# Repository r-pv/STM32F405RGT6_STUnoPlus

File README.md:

# STM32F405RGT6 STUno+

An ST development board based on the STM32F405RGT6/STM32F405RG (Clock: 168MHz, Flash: 1024Kb, Ram:194Kb) MCU (LQFP-64) compatible with STM32Duino (Arduino).

## Pinout:

## Files and Folders description

- **RBOARD_F405RGT6** it's the variant board for the STM32 Arduino Core.
- **rSTM32F405RGT6_B** it's the KiCAD 5.1.2 project.
- **rSTM32F405RGT6.schematic.pdf** the schematic.

## Install

- This requires the [STM32 core for arduino](https://github.com/stm32duino/Arduino_Core_STM32/), the ST original.
- I used this [guide to add the board](https://github.com/stm32duino/wiki/wiki/Add-a-new-variant-(board)), you can check it or continue with my suggestions to install the new board.
- Copy the **"RBOARD_F405RGT6"** folder to the Arduino **"variants"** folder, in win7 is located at: **c:\Users\\<USERNAME\>\AppData\Local\Arduino15\packages\STM32\hardware\stm32\1.8.0\variants**
- Edit the **"boards.txt"** file, in win7 is located at a lever up than the "variants" folder, search for the **Generic F4** board line and add the lines to leave it as I show you next:

```
# Adafruit Feather STM32F405 board
GenF4.menu.pnum.FEATHER_F405=Adafruit Feather STM32F405
GenF4.menu.pnum.FEATHER_F405.upload.maximum_size=1048576
GenF4.menu.pnum.FEATHER_F405.upload.maximum_data_size=131072
GenF4.menu.pnum.FEATHER_F405.build.board=FEATHER_F405
GenF4.menu.pnum.FEATHER_F405.build.product_line=STM32F405xx
GenF4.menu.pnum.FEATHER_F405.build.variant=FEATHER_F405

# STM32F405RGT6 STUnoPlus board
GenF4.menu.pnum.RBOARD_F405RGT6=STM32F405RGT6 STUnoPlus
GenF4.menu.pnum.RBOARD_F405RGT6.upload.maximum_size=1048576
GenF4.menu.pnum.RBOARD_F405RGT6.upload.maximum_data_size=131072
GenF4.menu.pnum.RBOARD_F405RGT6.build.board=RBOARD_F405RGT6
GenF4.menu.pnum.RBOARD_F405RGT6.build.product_line=STM32F405xx
GenF4.menu.pnum.RBOARD_F405RGT6.build.variant=RBOARD_F405RGT6
```
(add after the _"# Adafruit Feather STM32F405 board"_ section).

That's all.

So on the arduino IDE, on the **boards** menu pick the option _"Generic STM32F4 series"_ and the **board part number:** suboption pick the _"STM32F405RGT6 STUnoPlus"_ option.

**Note:** while adafruit board and mine use the same MCU there are not compatible variants: adafruit uses a 12mhz external crystal, mine uses an 8mhz.

## The real board

**Front**

_*I submerge the boards on a painters solvent bath to clean the flux residue which I haven't any problem until the DC jack came, as you see, didn't took the solvent bath kindly :P_

**Back**

_*The footprint for the second crystal (Y2) was wrong on this board but it's already corrected on the KiCAD files._

## Running some tests

The **STUno+** running the Adafruit ILI9341 library over hardware SPI.

_Video in progress..._

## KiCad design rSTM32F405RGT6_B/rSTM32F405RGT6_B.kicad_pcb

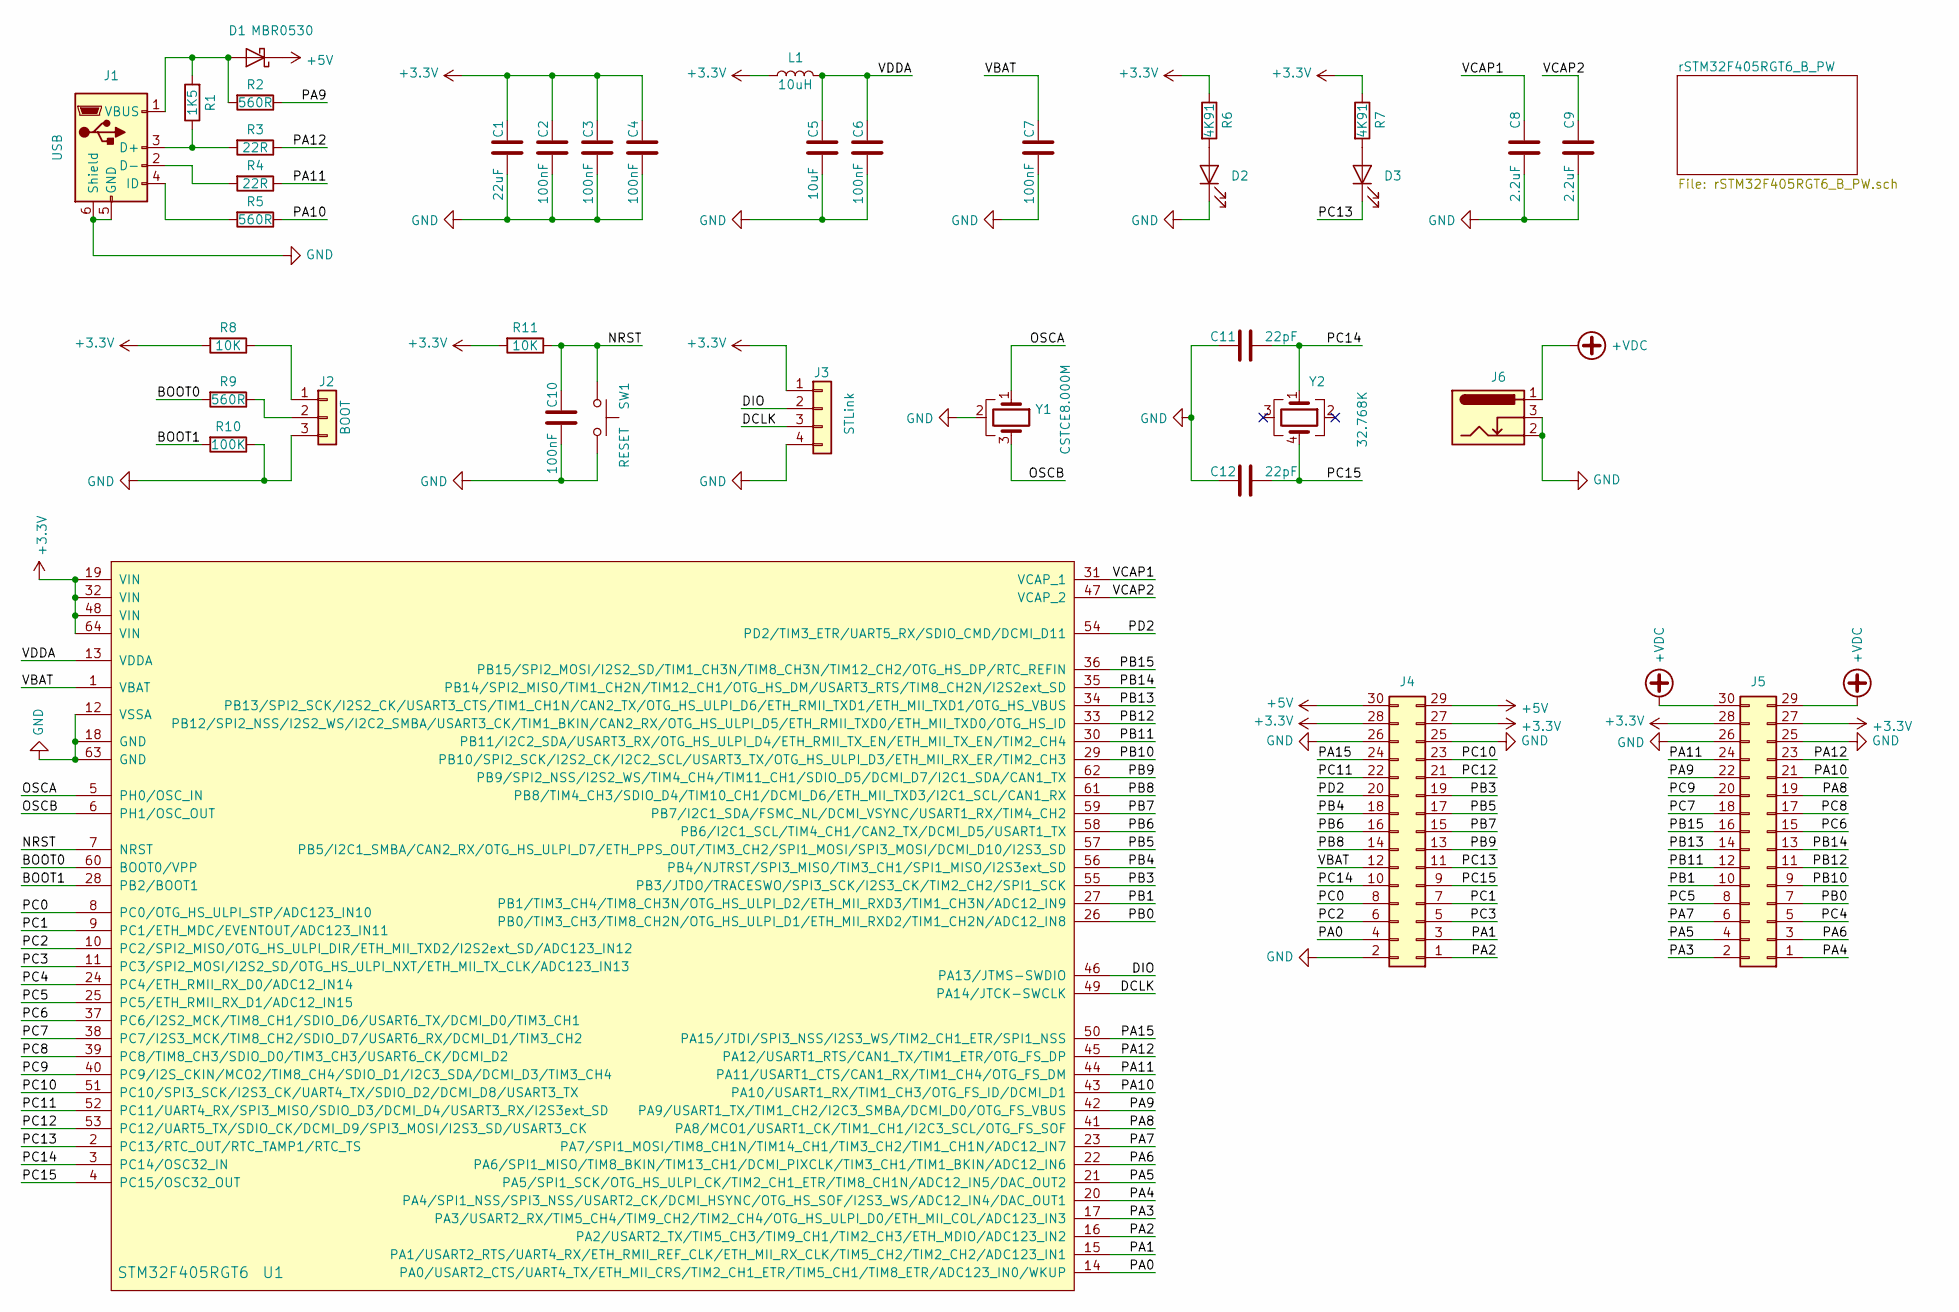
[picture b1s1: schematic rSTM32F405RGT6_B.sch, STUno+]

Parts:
C1: 22uF; C_0805
C2, C3, C4, C6, C7, C10: 100nF; C_0805
C5: 10uF; C_0805
C8, C9: 2.2uF; C_0603
C11, C12: 22pF; C_0805
D1: MBR0530; D_SOD-123
D2, D3: LED; LED_0805
J1: USB; USB_Micro-B_Molex_47346-0001
J2: BOOT; Pin_Header_Straight_1x03_Pitch2.54mm
J3: STLink; Pin_Header_Straight_1x04_Pitch2.54mm
J4, J5: Pin_Header_Straight_2x15_Pitch2.54mm
J6: JACK_ALIM
L1: 10uH; L_0805
R1: 1K5; R_0603
R2, R5, R9: 560R; R_0603
R3, R4: 22R; R_0603
R6, R7: 4K91; R_0603
R8, R11: 10K; R_0603
R10: 100K; R_0603
SW1: RESET; Switch_SMD_5.2x6.4_reset
U1: STM32F405RGT6; LQFP-64_10x10mm_Pitch0.5mm
Y1: CSTCE8.000M; Crystal_CSTCE_3pin_3.2x1.3
Y2: 32.768K; Crystal_4pin_SMD_2.5x4.6

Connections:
+3V3: C1.1, C2.1, C3.1, C4.1, J3.1, J4.27, J4.28, J5.27, J5.28, L1.1, R6.1, R7.1, R8.2, R11.2, U1.19 (VIN), U1.32 (VIN), U1.48 (VIN), U1.64 (VIN); also elsewhere on the board
+5V: D1.1 (K), J4.29, J4.30; also elsewhere on the board
+VDC: J5.29, J5.30, J6.1; also elsewhere on the board
/BOOT0: R9.2, U1.60 (BOOT0/VPP)
/BOOT1: R10.2, U1.28 (PB2/BOOT1)
/DCLK: J3.3, U1.49 (PA14/JTCK-SWCLK)
/DIO: J3.2, U1.46 (PA13/JTMS-SWDIO)
/NRST: C10.1, R11.1, SW1.1, U1.7 (NRST)
/OSCA: U1.5 (PH0/OSC_IN), Y1.1
/OSCB: U1.6 (PH1/OSC_OUT), Y1.3
/PA0: J4.4, U1.14 (PA0/USART2_CTS/UART4_TX/ETH_MII_CRS/TIM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)
/PA1: J4.3, U1.15 (PA1/USART2_RTS/UART4_RX/ETH_RMII_REF_CL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)
/PA2: J4.1, U1.16 (PA2/USART2_TX/TIM5_CH3/TIM9_CH1/TIM2_CH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)
/PA3: J5.2, U1.17 (PA3/USART2_RX/TIM5_CH4/TIM9_CH2/TIM2_CH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)
/PA4: J5.1, U1.20 (PA4/SPI1_NSS/SPI3_NSS/USART2_CK/DCMI_HS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)
/PA5: J5.4, U1.21 (PA5/SPI1_SCK/OTG_HS_ULPI_CK/TIM2_CH1_ET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)
/PA6: J5.3, U1.22 (PA6/SPI1_MISO/TIM8_BKIN/TIM13_CH1/DCMI_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)
/PA7: J5.6, U1.23 (PA7/SPI1_MOSI/TIM8_CH1N/TIM14_CH1/TIM3_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)
/PA8: J5.19, U1.41 (PA8/MCO1/USART1_CK/TIM1_CH1/I2C3_SCL/OT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)
/PA9: J5.22, R2.1, U1.42 (PA9/USART1_TX/TIM1_CH2/I2C3_SMBA/DCMI_D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)
/PA10: J5.21, R5.1, U1.43 (PA10/USART1_RX/TIM1_CH3/OTG_FS_ID/DCMI_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)
/PA11: J5.24, R4.1, U1.44 (PA11/USART1_CTS/CAN1_RX/TIM1_CH4/OTG_FS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)
/PA12: J5.23, R3.1, U1.45 (PA12/USART1_RTS/CAN1_TX/TIM1_ETR/OTG_FS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)
/PA15: J4.24, U1.50 (PA15/JTDI/SPI3_NSS/I2S3_WS/TIM2_CH1_ETR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)
/PB0: J5.7, U1.26 (PB0/TIM3_CH3/TIM8_CH2N/OTG_HS_ULPI_D1/E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)
/PB1: J5.10, U1.27 (PB1/TIM3_CH4/TIM8_CH3N/OTG_HS_ULPI_D2/E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)
/PB3: J4.19, U1.55 (PB3/JTDO/TRACESWO/SPI3_SCK/I2S3_CK/TIM2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)
/PB4: J4.18, U1.56 (PB4/NJTRST/SPI3_MISO/TIM3_CH1/SPI1_MISO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)
/PB5: J4.17, U1.57 (PB5/I2C1_SMBA/CAN2_RX/OTG_HS_ULPI_D7/ET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)
/PB6: J4.16, U1.58 (PB6/I2C1_SCL/TIM4_CH1/CAN2_TX/DCMI_D5/U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)
/PB7: J4.15, U1.59 (PB7/I2C1_SDA/FSMC_NL/DCMI_VSYNC/USART1_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)
/PB8: J4.14, U1.61 (PB8/TIM4_CH3/SDIO_D4/TIM10_CH1/DCMI_D6/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)
/PB9: J4.13, U1.62 (PB9/SPI2_NSS/I2S2_WS/TIM4_CH4/TIM11_CH1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)
/PB10: J5.9, U1.29 (PB10/SPI2_SCK/I2S2_CK/I2C2_SCL/USART3_T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)
/PB11: J5.12, U1.30 (PB11/I2C2_SDA/USART3_RX/OTG_HS_ULPI_D4/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)
/PB12: J5.11, U1.33 (PB12/SPI2_NSS/I2S2_WS/I2C2_SMBA/USART3_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)
/PB13: J5.14, U1.34 (PB13/SPI2_SCK/I2S2_CK/USART3_CTS/TIM1_C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)
/PB14: J5.13, U1.35 (PB14/SPI2_MISO/TIM1_CH2N/TIM12_CH1/OTG_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)
/PB15: J5.16, U1.36 (PB15/SPI2_MOSI/I2S2_SD/TIM1_CH3N/TIM8_C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)
/PC0: J4.8, U1.8 (PC0/OTG_HS_ULPI_STP/ADC123_IN10)
/PC1: J4.7, U1.9 (PC1/ETH_MDC/EVENTOUT/ADC123_IN11)
/PC2: J4.6, U1.10 (PC2/SPI2_MISO/OTG_HS_ULPI_DIR/ETH_MII_T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)
/PC3: J4.5, U1.11 (PC3/SPI2_MOSI/I2S2_SD/OTG_HS_ULPI_NXT/E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)
/PC4: J5.5, U1.24 (PC4/ETH_RMII_RX_D0/ADC12_IN14)
/PC5: J5.8, U1.25 (PC5/ETH_RMII_RX_D1/ADC12_IN15)
/PC6: J5.15, U1.37 (PC6/I2S2_MCK/TIM8_CH1/SDIO_D6/USART6_TX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)
/PC7: J5.18, U1.38 (PC7/I2S3_MCK/TIM8_CH2/SDIO_D7/USART6_RX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)
/PC8: J5.17, U1.39 (PC8/TIM8_CH3/SDIO_D0/TIM3_CH3/USART6_CK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)
/PC9: J5.20, U1.40 (PC9/I2S_CKIN/MCO2/TIM8_CH4/SDIO_D1/I2C3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)
/PC10: J4.23, U1.51 (PC10/SPI3_SCK/I2S3_CK/UART4_TX/SDIO_D2/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)
/PC11: J4.22, U1.52 (PC11/UART4_RX/SPI3_MISO/SDIO_D3/DCMI_D4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)
/PC12: J4.21, U1.53 (PC12/UART5_TX/SDIO_CK/DCMI_D9/SPI3_MOSI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)
/PC13: D3.1 (K), J4.11, U1.2 (PC13/RTC_OUT/RTC_TAMP1/RTC_TS)
/PC14: C11.1, J4.10, U1.3 (PC14/OSC32_IN), Y2.1
/PC15: C12.1, J4.9, U1.4 (PC15/OSC32_OUT), Y2.4
/PD2: J4.20, U1.54 (PD2/TIM3_ETR/UART5_RX/SDIO_CMD/DCMI_D11)
/VBAT: C7.1, J4.12, U1.1 (VBAT)
/VCAP1: C8.1, U1.31 (VCAP_1)
/VCAP2: C9.1, U1.47 (VCAP_2)
/VDDA: C5.1, C6.1, L1.2, U1.13 (VDDA)
GND: C1.2, C2.2, C3.2, C4.2, C5.2, C6.2, C7.2, C8.2, C9.2, C10.2, C11.2, C12.2, D2.1 (K), J1.5 (GND), J1.6 (Shield), J2.3, J3.4, J4.2, J4.25, J4.26, J5.25, J5.26, J6.2, J6.3, R10.1, SW1.2, U1.12 (VSSA), U1.18 (GND), U1.63 (GND), Y1.2; also elsewhere on the board
unnamed: D1.2 (A), J1.1 (VBUS), R1.2, R2.2
unnamed: D2.2 (A), R6.2
unnamed: D3.2 (A), R7.2
unnamed: J1.2 (D-), R4.2
unnamed: J1.3 (D+), R1.1, R3.2
unnamed: J1.4 (ID), R5.2
unnamed: J2.1, R8.1
unnamed: J2.2, R9.1

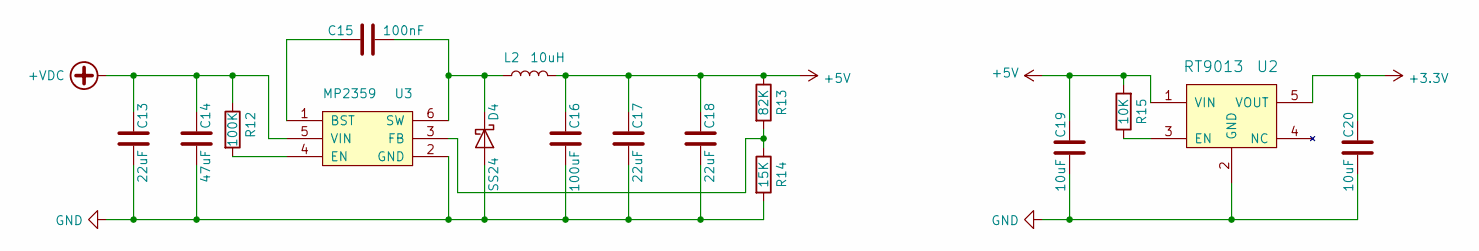
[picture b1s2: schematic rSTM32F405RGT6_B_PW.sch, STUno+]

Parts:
C13, C17, C18: 22uF; C_0805
C14: 47uF; C_1206
C15: 100nF; C_0805
C16: 100uF; C_1206
C19, C20: 10uF; C_0805
D4: SS24; D_SMA
L2: 10uH; Inductor-CD54
R12: 100K; R_0603
R13: 82K; R_0603
R14: 15K; R_0603
R15: 10K; R_0603
U2: RT9013; SOT-23-5
U3: MP2359; SOT-23-6

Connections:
+3V3: C20.1, U2.5 (VOUT); also elsewhere on the board
+5V: C16.1, C17.1, C18.1, C19.1, L2.2, R13.1, R15.2, U2.1 (VIN); also elsewhere on the board
+VDC: C13.1, C14.1, R12.1, U3.5 (VIN); also elsewhere on the board
GND: C13.2, C14.2, C16.2, C17.2, C18.2, C19.2, C20.2, D4.2 (A), R14.2, U2.2 (GND), U3.2 (GND); also elsewhere on the board
unnamed: C15.1, D4.1 (K), L2.1, U3.6 (SW)
unnamed: C15.2, U3.1 (BST)
unnamed: R12.2, U3.4 (EN)
unnamed: R13.2, R14.1, U3.3 (FB)
unnamed: R15.1, U2.3 (EN)

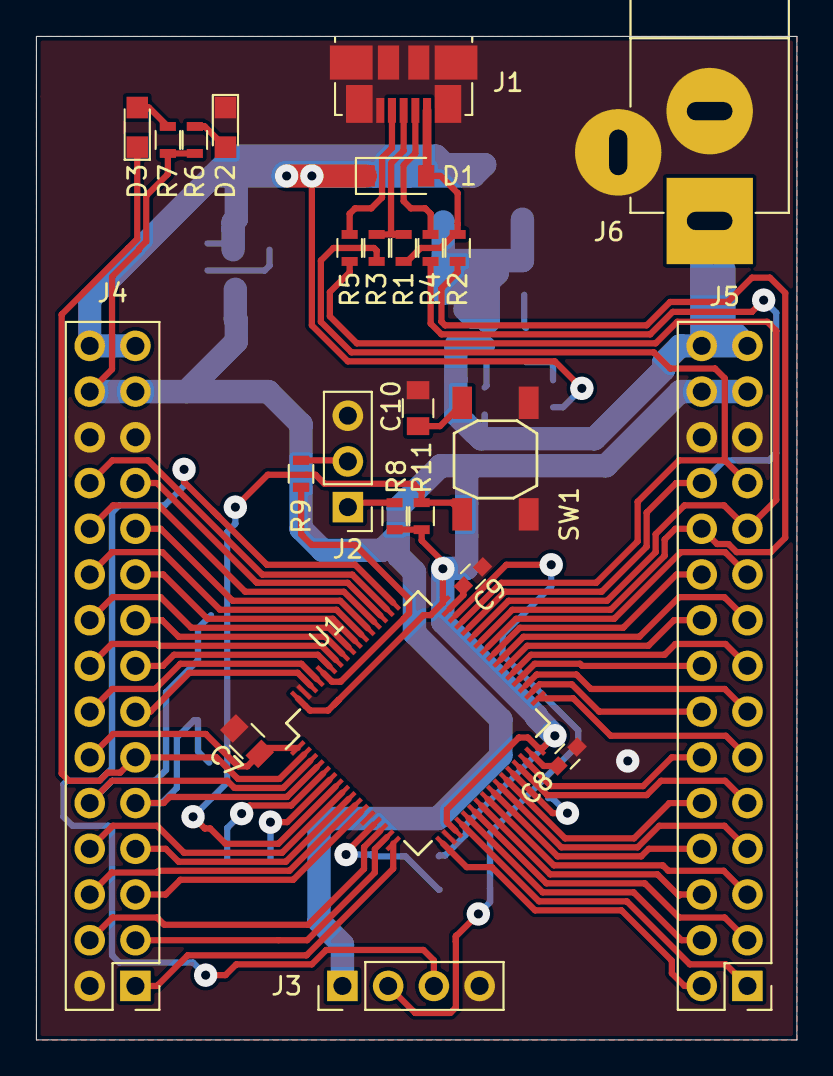
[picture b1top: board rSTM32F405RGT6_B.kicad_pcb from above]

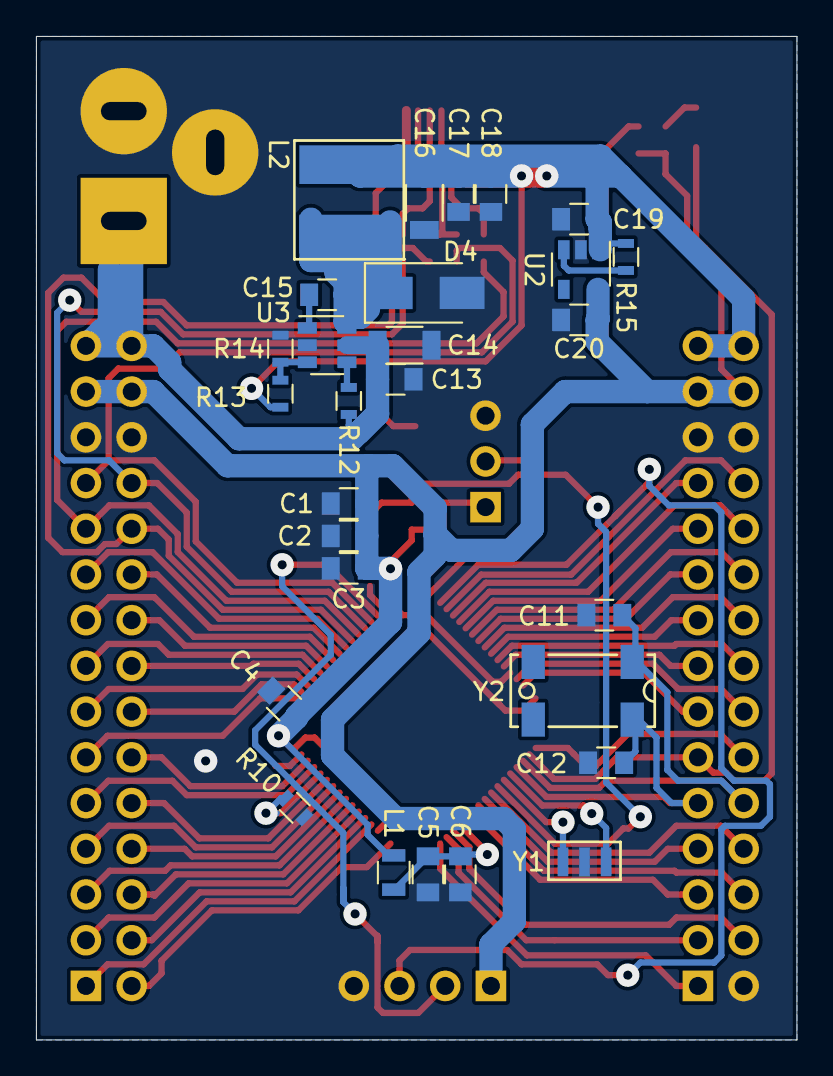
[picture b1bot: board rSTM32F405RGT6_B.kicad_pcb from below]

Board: 2 copper layers, 42.2 x 55.8 mm, 53 parts (28 on the bottom side), 74 nets.

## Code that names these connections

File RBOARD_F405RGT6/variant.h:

/*
 *******************************************************************************
 * Copyright (c) 2017, STMicroelectronics
 * All rights reserved.
 *
 * Redistribution and use in source and binary forms, with or without
 * modification, are permitted provided that the following conditions are met:
 *
 * 1. Redistributions of source code must retain the above copyright notice,
 *    this list of conditions and the following disclaimer.
 * 2. Redistributions in binary form must reproduce the above copyright notice,
 *    this list of conditions and the following disclaimer in the documentation
 *    and/or other materials provided with the distribution.
 * 3. Neither the name of STMicroelectronics nor the names of its contributors
 *    may be used to endorse or promote products derived from this software
 *    without specific prior written permission.
 *
 * THIS SOFTWARE IS PROVIDED BY THE COPYRIGHT HOLDERS AND CONTRIBUTORS "AS IS"
 * AND ANY EXPRESS OR IMPLIED WARRANTIES, INCLUDING, BUT NOT LIMITED TO, THE
 * IMPLIED WARRANTIES OF MERCHANTABILITY AND FITNESS FOR A PARTICULAR PURPOSE ARE
 * DISCLAIMED. IN NO EVENT SHALL THE COPYRIGHT HOLDER OR CONTRIBUTORS BE LIABLE
 * FOR ANY DIRECT, INDIRECT, INCIDENTAL, SPECIAL, EXEMPLARY, OR CONSEQUENTIAL
 * DAMAGES (INCLUDING, BUT NOT LIMITED TO, PROCUREMENT OF SUBSTITUTE GOODS OR
 * SERVICES; LOSS OF USE, DATA, OR PROFITS; OR BUSINESS INTERRUPTION) HOWEVER
 * CAUSED AND ON ANY THEORY OF LIABILITY, WHETHER IN CONTRACT, STRICT LIABILITY,
 * OR TORT (INCLUDING NEGLIGENCE OR OTHERWISE) ARISING IN ANY WAY OUT OF THE USE
 * OF THIS SOFTWARE, EVEN IF ADVISED OF THE POSSIBILITY OF SUCH DAMAGE.
 *******************************************************************************
 */
#ifndef _VARIANT_ARDUINO_STM32_
#define _VARIANT_ARDUINO_STM32_

/*----------------------------------------------------------------------------
 *        Headers
 *----------------------------------------------------------------------------*/
#ifdef __cplusplus
extern "C"{
#endif // __cplusplus

/*----------------------------------------------------------------------------
 *        Pins
 *----------------------------------------------------------------------------*/
//.with.the.USB.on.top.and.bottom-to-left-to-right.naming;
//.this.weird.naming.due.to.comply.with.the.analog.pin.number.being>=NUM_ANALOG_INPUTS.in.this.case:16
// Bottom.side
#define PA13   0
#define PA14   1
// Left.Side
#define PA15   2
#define PC10   3
#define PC11   4
#define PC12   5
#define PD2    6
#define PB3    7
#define PB4    8
#define PB5    9
#define PB6    10
#define PB7    11
#define PB8    12
#define PB9    13
//VBAT
#define PC13   14
#define PC14   15
#define PC15   16
#define PC0    17
#define PC1    18
#define PC2    19
#define PC3    20
#define PA0    21
#define PA1    22
//GND
#define PA2    23
// Right.side
#define PA3    24
#define PA4    25
#define PA5    26
#define PA6    27
#define PA7    28
#define PC4    29
#define PC5    30
#define PB0    31
#define PB1    32
#define PB10   33
#define PB11   34
#define PB12   35
#define PB13   36
#define PB14   37
#define PB15   38
#define PC6    39
#define PC7    40
#define PC8    41
#define PC9    42
#define PA8    43
#define PA9    44
#define PA10   45
#define PA11   46
#define PA12   47

// Define pin names to match digital pin number --> Dx
// It could be used with preprocessor tests (e.g. #if PXn == 3)
// so an enum will not work.
// !!!
// !!! Copy the digitalPin[] array from the variant.cpp
// !!! and remove all '_': PX_n --> PXn
// !!! For NC, comment the line to warn x pin number is NC
// !!! // x is NC
// !!! For duplicated pin name, comment the line to warn x pin number
// !!! is PXn which is already defined with y pin number
// !!! // x is PXn (y)
// !!! Ex:
// !!! ...
// !!! #define PA4  20 // A14
// !!! #define PB4  21
// !!! #define PB5  22
// !!! #define PB3  23
// !!! // 24 is PA4 (20)
// !!! // 25 is PB4 (21)
// !!! #define PA2  26 // A15
// !!! ...
//#define PXn x

// This must be a literal
// It is used with preprocessor tests (e.g. #if NUM_DIGITAL_PINS > 3)
// so an enum will not work.
#define NUM_DIGITAL_PINS        57

// Allow to define Arduino style alias for analog input pin number --> Ax
// All pins are digital, analog inputs are a subset of digital pins
// and must be contiguous to be able to loop on each value
// This must be a literal with a value less than or equal to MAX_ANALOG_INPUTS
// defined in pin_arduino.h
// It is used with preprocessor tests (e.g. #if NUM_ANALOG_INPUTS > 3)
// so an enum will not work.
// !!!
// !!! It must be aligned with the number of analog PinName
// !!! defined in digitalPin[] array in variant.cpp
// !!!
#define NUM_ANALOG_INPUTS       16
// Define digital pin number of the first analog input  (i.e. which digital pin is A0)
// First analog pin value (A0) must be greater than or equal to NUM_ANALOG_INPUTS
#define NUM_ANALOG_FIRST        17

// Below ADC, DAC and PWM definitions already done in the core
// Could be redefined here if needed
// ADC resolution is 12bits
//#define ADC_RESOLUTION          12
//#define DACC_RESOLUTION         12

// PWM resolution
//#define PWM_RESOLUTION          8
//#define PWM_FREQUENCY           1000
//#define PWM_MAX_DUTY_CYCLE      255

// On-board LED pin number
#define LED_BUILTIN             PC13
#define LED_GREEN               LED_BUILTIN

// On-board user button
#define USER_BTN                x

// Below SPI and I2C definitions already done in the core
// Could be redefined here if differs from the default one
// SPI Definitions
// SPI Definitions
#define PIN_SPI_SS              PA4
#define PIN_SPI_MOSI            PA7
#define PIN_SPI_MISO            PA6
#define PIN_SPI_SCK             PA5

// I2C Definitions
#define PIN_WIRE_SDA            PB7  // Default for Arduino connector compatibility
#define PIN_WIRE_SCL            PB6  // Default for Arduino connector compatibility

// Timer Definitions
// Do not use timer used by PWM pins when possible. See PinMap_PWM.
#define TIMER_TONE              TIM3

// Do not use basic timer: OC is required
#define TIMER_SERVO             TIM2  //TODO: advanced-control timers don't work

// UART Definitions
#define SERIAL_UART_INSTANCE    1
// Default pin used for 'Serial' instance
// Mandatory for Firmata
#define PIN_SERIAL_RX           PA10
#define PIN_SERIAL_TX           PA9

// UART Definitions
// Define here Serial instance number to map on Serial generic name
//#define SERIAL_UART_INSTANCE    x //ex: 2 for Serial2 (USART2)
// DEBUG_UART could be redefined to print on another instance than 'Serial'
//#define DEBUG_UART              ((USART_TypeDef *) U(S)ARTX) // ex: USART3
// DEBUG_UART baudrate, default: 9600 if not defined
//#define DEBUG_UART_BAUDRATE     x
// DEBUG_UART Tx pin name, default: the first one found in PinMap_UART_TX for DEBUG_UART
//#define DEBUG_PINNAME_TX        PX_n // PinName used for TX


// Optional PIN_SERIALn_RX and PIN_SERIALn_TX where 'n' is the U(S)ART number
// Used when user instanciate a hardware Serial using its peripheral name.
// Example: HardwareSerial mySerial(USART3);
// will use PIN_SERIAL3_RX and PIN_SERIAL3_TX if defined.
//#define PIN_SERIALn_RX          x // For U(S)ARTn RX
//#define PIN_SERIALn_TX          x // For U(S)ARTn TX
//#define PIN_SERIALLP1_RX        x // For LPUART1 RX
//#define PIN_SERIALLP1_TX        x // For LPUART1 TX

// SD card slot Definitions
// SD detect signal can be defined if required
//#define SD_DETECT_PIN           x
// SD Read/Write timeout, default value defined in STM32SD library
//#define SD_DATATIMEOUT          x

#ifdef __cplusplus
} // extern "C"
#endif
/*----------------------------------------------------------------------------
 *        Arduino objects - C++ only
 *----------------------------------------------------------------------------*/

#ifdef __cplusplus
// These serial port names are intended to allow libraries and architecture-neutral
// sketches to automatically default to the correct port name for a particular type
// of use.  For example, a GPS module would normally connect to SERIAL_PORT_HARDWARE_OPEN,
// the first hardware serial port whose RX/TX pins are not dedicated to another use.
//
// SERIAL_PORT_MONITOR        Port which normally prints to the Arduino Serial Monitor
//
// SERIAL_PORT_USBVIRTUAL     Port which is USB virtual serial
//
// SERIAL_PORT_LINUXBRIDGE    Port which connects to a Linux system via Bridge library
//
// SERIAL_PORT_HARDWARE       Hardware serial port, physical RX & TX pins.
//
// SERIAL_PORT_HARDWARE_OPEN  Hardware serial ports which are open for use.  Their RX & TX
//                            pins are NOT connected to anything by default.
#define SERIAL_PORT_MONITOR     Serial
#define SERIAL_PORT_HARDWARE    Serial
#endif

#endif /* _VARIANT_ARDUINO_STM32_ */

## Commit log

2019-09-01 KiCAD project.
2019-09-04 KiCAD Project
    Fixing some footprints.
2019-09-04 Update pinout.
2019-09-05 isn't required.
2019-09-05 updates variant.
2019-09-12 small fix.
2019-10-24 Pinout updated: added ADC and PWM pins.
2019-10-25 Fixed a bug with the analogs.
    Fixed a mistake I made.
2020-02-27 Updated install info.
